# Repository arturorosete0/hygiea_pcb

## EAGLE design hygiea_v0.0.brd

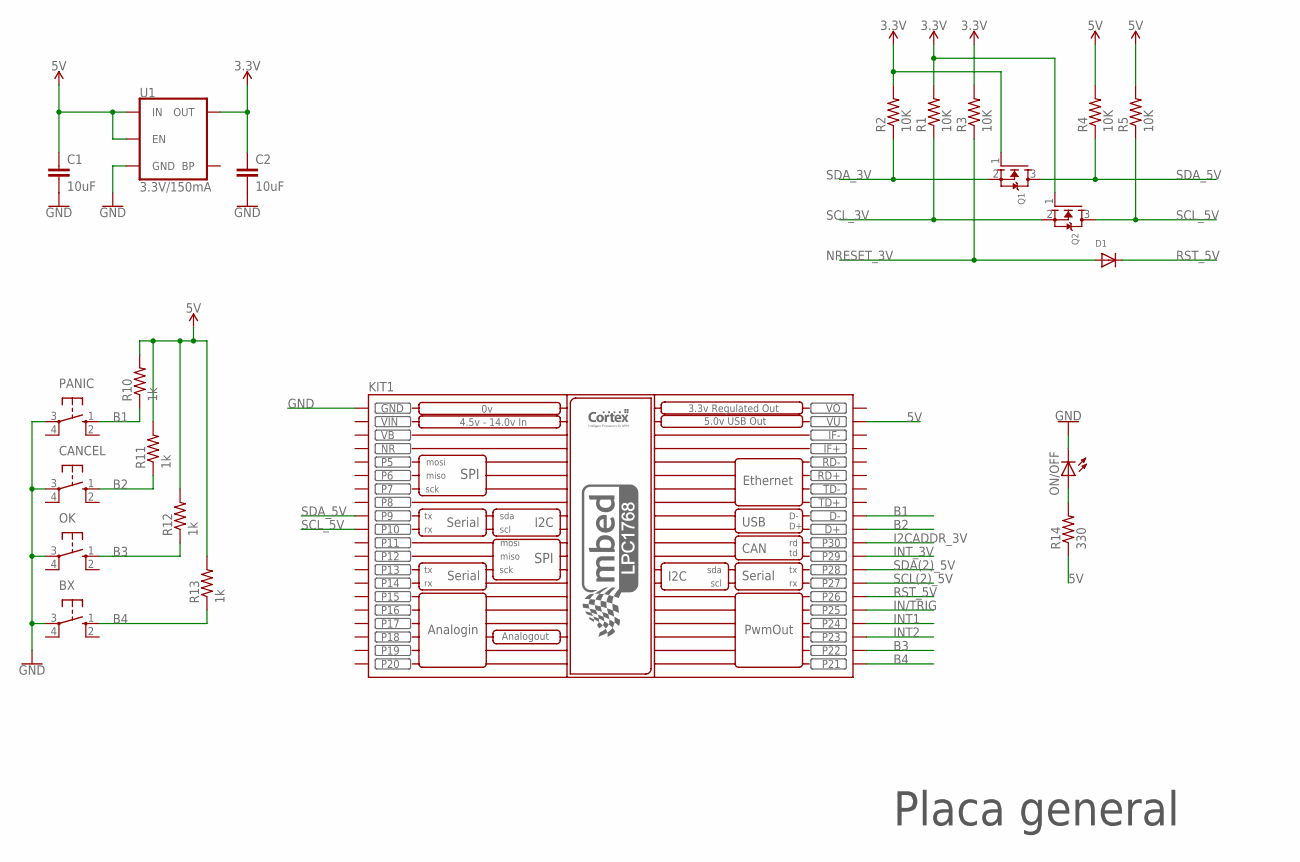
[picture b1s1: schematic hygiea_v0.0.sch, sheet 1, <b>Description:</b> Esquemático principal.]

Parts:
BX: 10-XX; B3F-10XX
C1, C2: 10uF; C0805
CANCEL: 10-XX; B3F-10XX
D1: DIODESOD-323F; SOD-323F
KIT1: MBED_NXP_LPC1768; MBED-KIT
OK: 10-XX; B3F-10XX
ON/OFF: LEDCHIP-LED0805; CHIP-LED0805
PANIC: 10-XX; B3F-10XX
Q1, Q2: MOSFET-NWAVE; SOT23-W
R1, R2, R3, R4, R5: 10K; R0805
R10, R11, R12, R13: 1k; R0805
R14: 330; R0805
U1: 3.3V/150mA; SOT23-5

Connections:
3.3V: C2.1, Q1.1 (G), Q2.1 (G), R1.2, R2.2, R3.2, U1.5 (OUT); also elsewhere on the board
5V: C1.1, KIT1.VU, R4.2, R5.2, R10.2, R11.2, R12.2, R13.2, R14.1, U1.1 (IN), U1.3 (EN); also elsewhere on the board
B1: KIT1.D-, PANIC.1 (S), R10.1
B2: CANCEL.1 (S), KIT1.D+, R11.1
B3: KIT1.P$22 (P22), OK.1 (S), R12.1
B4: BX.1 (S), KIT1.P$21 (P21), R13.1
GND: BX.3, C1.2, C2.2, CANCEL.3, KIT1.GND, OK.3, ON/OFF.C, PANIC.3, U1.2 (GND); also elsewhere on the board
I2CADDR_3V: KIT1.P$30 (P30); also elsewhere on the board
IN/TRIG: KIT1.P$25 (P25); also elsewhere on the board
INT1: KIT1.P$24 (P24); also elsewhere on the board
INT2: KIT1.P$23 (P23); also elsewhere on the board
INT_3V: KIT1.P$29 (P29); also elsewhere on the board
unnamed: ON/OFF.A, R14.2
NR: KIT1.NR
NRESET_3V: D1.A, R3.1; also elsewhere on the board
RST_5V: D1.C, KIT1.P$26 (P26)
SCL(2)_5V: KIT1.P$27 (P27); also elsewhere on the board
SCL_3V: Q2.2 (S), R1.1; also elsewhere on the board
SCL_5V: KIT1.P$10 (P10), Q2.3 (D), R5.1; also elsewhere on the board
SDA(2)_5V: KIT1.P$28 (P28); also elsewhere on the board
SDA_3V: Q1.2 (S), R2.1; also elsewhere on the board
SDA_5V: KIT1.P$9 (P9), Q1.3 (D), R4.1; also elsewhere on the board
VB: KIT1.VB
VIN: KIT1.VIN
VO: KIT1.VOUT (VO)

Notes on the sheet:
Placa general

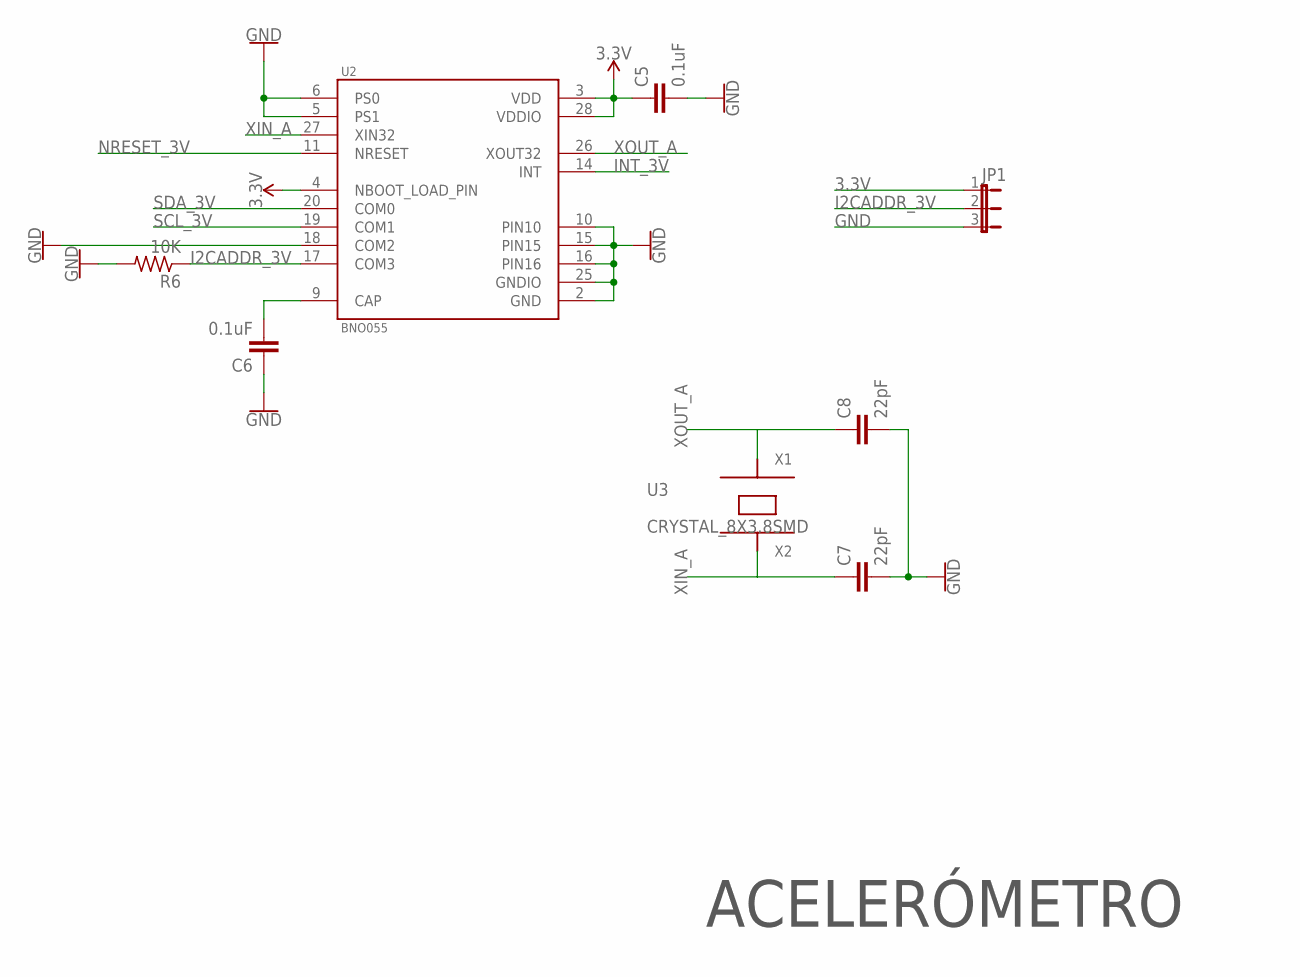
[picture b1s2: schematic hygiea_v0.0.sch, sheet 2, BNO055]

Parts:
C5, C6: 0.1uF; C0805
C7, C8: 22pF; C0805
JP1: JP2E; JP2
R6: 10K; R0805
U2: BNO055; LGA28R50P4X10_380X520X100
U3: CRYSTAL_8X3.8SMD; PM8.0X3.8MM

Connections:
3.3V: C5.1, JP1.1, U2.3 (VDD), U2.4 (NBOOT_LOAD_PIN), U2.28 (VDDIO); also elsewhere on the board
GND: C5.2, C6.1, C7.2, C8.2, JP1.3, R6.2, U2.2 (GND), U2.5 (PS1), U2.6 (PS0), U2.10 (PIN10), U2.15 (PIN15), U2.16 (PIN16), U2.18 (COM2), U2.25 (GNDIO); also elsewhere on the board
I2CADDR_3V: JP1.2, R6.1, U2.17 (COM3); also elsewhere on the board
INT_3V: U2.14 (INT); also elsewhere on the board
unnamed: C6.2, U2.9 (CAP)
NRESET_3V: U2.11 (NRESET); also elsewhere on the board
SCL_3V: U2.19 (COM1); also elsewhere on the board
SDA_3V: U2.20 (COM0); also elsewhere on the board
XIN_A: C7.1, U2.27 (XIN32), U3.4 (X2)
XOUT_A: C8.1, U2.26 (XOUT32), U3.1 (X1)

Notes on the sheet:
ACELERÓMETRO

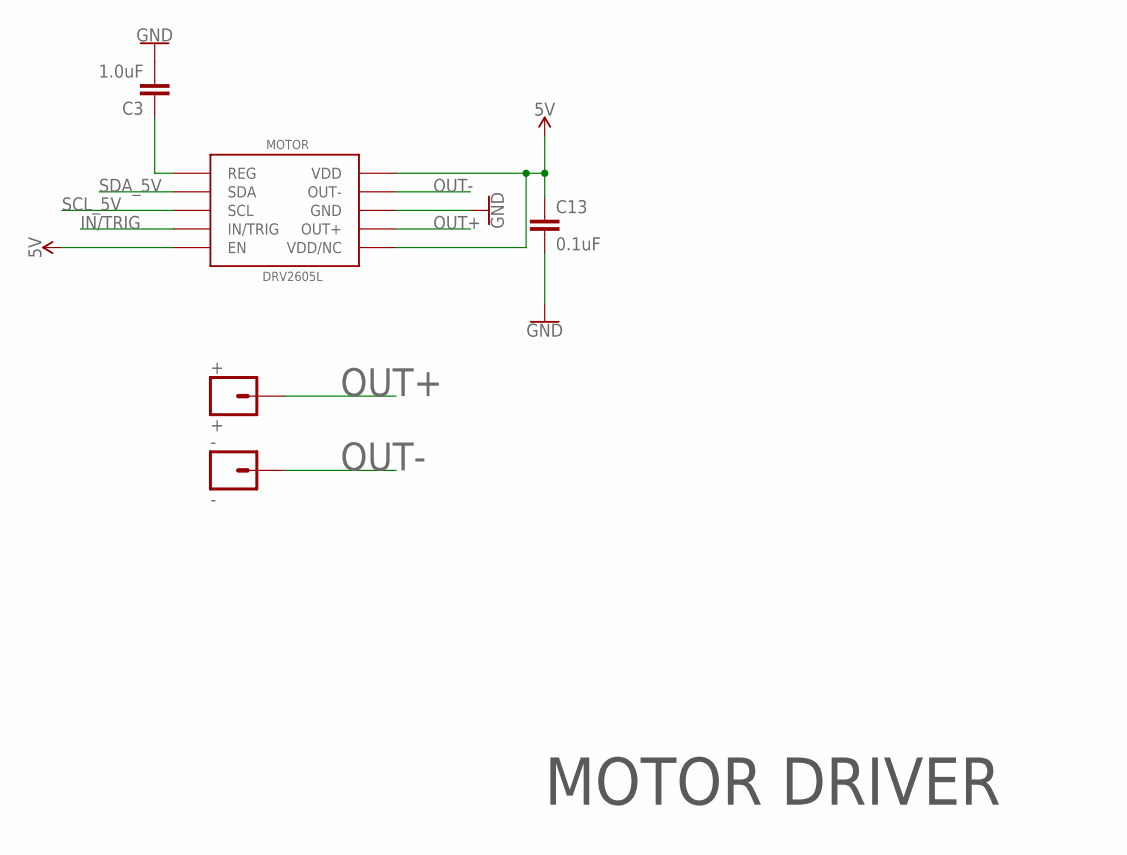
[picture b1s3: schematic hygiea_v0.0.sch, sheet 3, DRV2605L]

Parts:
+: +; 1X01_OFFSET
-: -; 1X01_OFFSET
C3: 1.0uF; C0805
C13: 0.1uF; C0805
MOTOR: DRV2605L; VSSOP-10

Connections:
5V: C13.1, MOTOR.P$5 (EN), MOTOR.P$6 (VDD/NC), MOTOR.P$10 (VDD); also elsewhere on the board
GND: C3.2, C13.2, MOTOR.P$8 (GND); also elsewhere on the board
IN/TRIG: MOTOR.P$4 (IN/TRIG); also elsewhere on the board
unnamed: C3.1, MOTOR.P$1 (REG)
OUT+: +.1, MOTOR.P$7 (OUT+)
OUT-: -.1, MOTOR.P$9 (OUT-)
SCL_5V: MOTOR.P$2 (SCL); also elsewhere on the board
SDA_5V: MOTOR.P$3 (SDA); also elsewhere on the board

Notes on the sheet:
MOTOR DRIVER

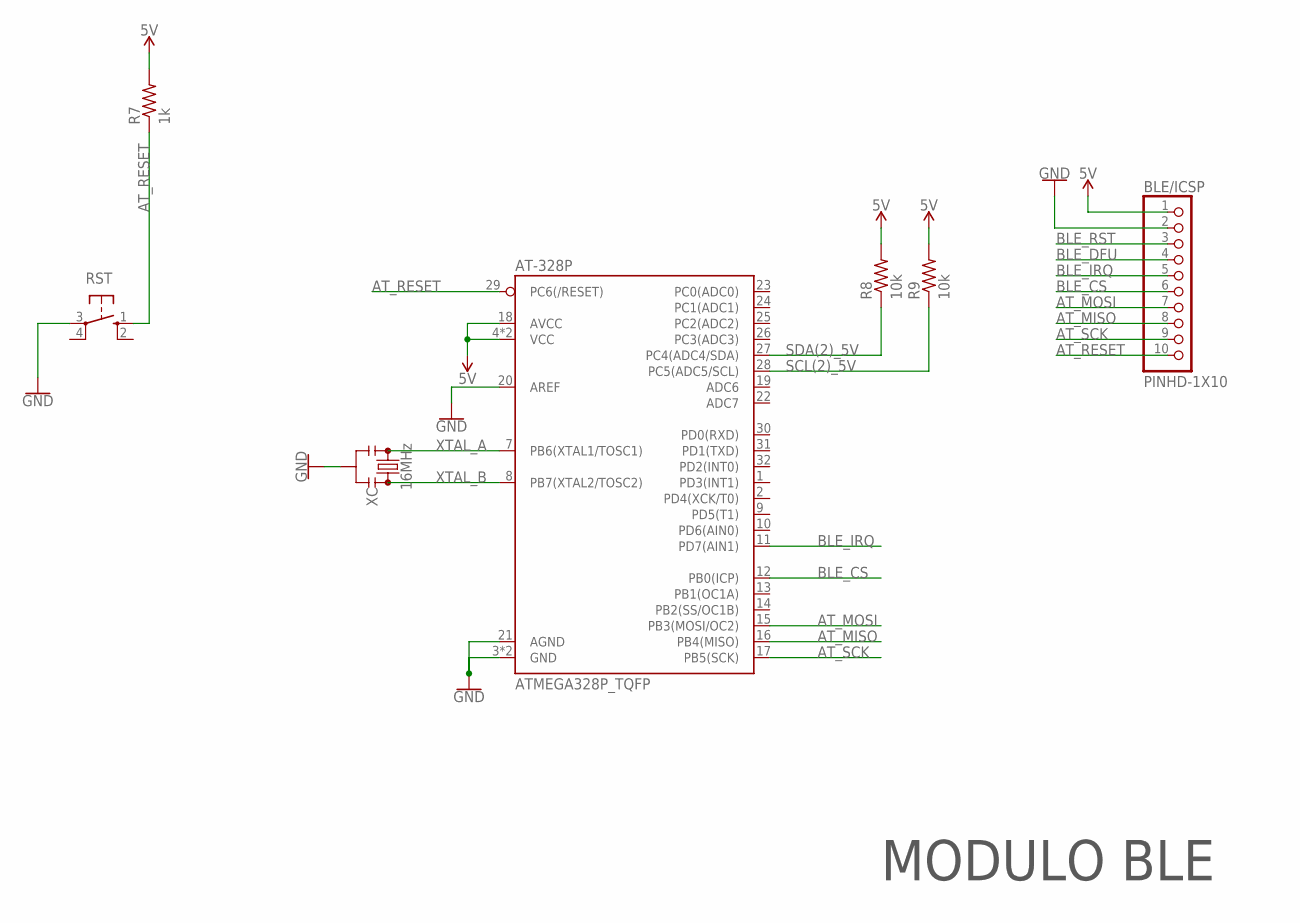
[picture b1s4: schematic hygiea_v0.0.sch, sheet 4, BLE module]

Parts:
AT-328P: ATMEGA328P_TQFP; TQFP32-08
BLE/ICSP: PINHD-1X10; 1X10-BIG
R7: 1k; R0805
R8, R9: 10k; R0805
RST: 10-XX; B3F-10XX
XC: 16MHz; RESONATOR-SMD-3.2X1.3

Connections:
5V: AT-328P.4 (VCC), AT-328P.6 (VCC), AT-328P.18 (AVCC), BLE/ICSP.1, R7.2, R8.2, R9.2; also elsewhere on the board
AT_MISO: AT-328P.16 (PB4(MISO)), BLE/ICSP.8
AT_MOSI: AT-328P.15 (PB3(MOSI/OC2)), BLE/ICSP.7
AT_RESET: AT-328P.29 (PC6(/RESET)), BLE/ICSP.10, R7.1, RST.1 (S)
AT_SCK: AT-328P.17 (PB5(SCK)), BLE/ICSP.9
BLE_CS: AT-328P.12 (PB0(ICP)), BLE/ICSP.6
BLE_DFU: BLE/ICSP.4
BLE_IRQ: AT-328P.11 (PD7(AIN1)), BLE/ICSP.5
BLE_RST: BLE/ICSP.3
GND: AT-328P.3 (GND), AT-328P.5 (GND), AT-328P.20 (AREF), AT-328P.21 (AGND), BLE/ICSP.2, RST.3, XC.2; also elsewhere on the board
SCL(2)_5V: AT-328P.28 (PC5(ADC5/SCL)), R9.1; also elsewhere on the board
SDA(2)_5V: AT-328P.27 (PC4(ADC4/SDA)), R8.1; also elsewhere on the board
XTAL_A: AT-328P.7 (PB6(XTAL1/TOSC1)), XC.3
XTAL_B: AT-328P.8 (PB7(XTAL2/TOSC2)), XC.1

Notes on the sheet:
MODULO BLE

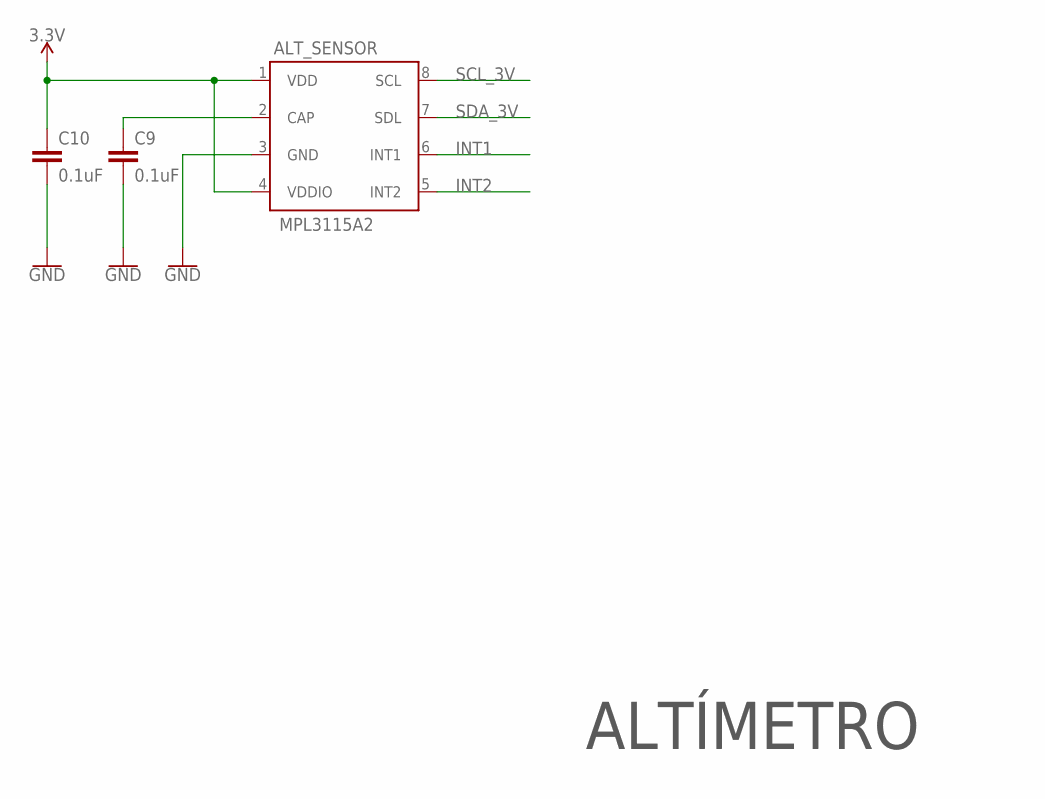
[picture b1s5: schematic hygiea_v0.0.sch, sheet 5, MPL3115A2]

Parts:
ALT_SENSOR: MPL3115A2; LGA8
C9, C10: 0.1uF; C0805

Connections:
3.3V: ALT_SENSOR.1 (VDD), ALT_SENSOR.4 (VDDIO), C10.1; also elsewhere on the board
GND: ALT_SENSOR.3 (GND), C9.2, C10.2; also elsewhere on the board
INT1: ALT_SENSOR.6 (INT1); also elsewhere on the board
INT2: ALT_SENSOR.5 (INT2); also elsewhere on the board
unnamed: ALT_SENSOR.2 (CAP), C9.1
SCL_3V: ALT_SENSOR.8 (SCL); also elsewhere on the board
SDA_3V: ALT_SENSOR.7 (SDL); also elsewhere on the board

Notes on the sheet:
ALTÍMETRO

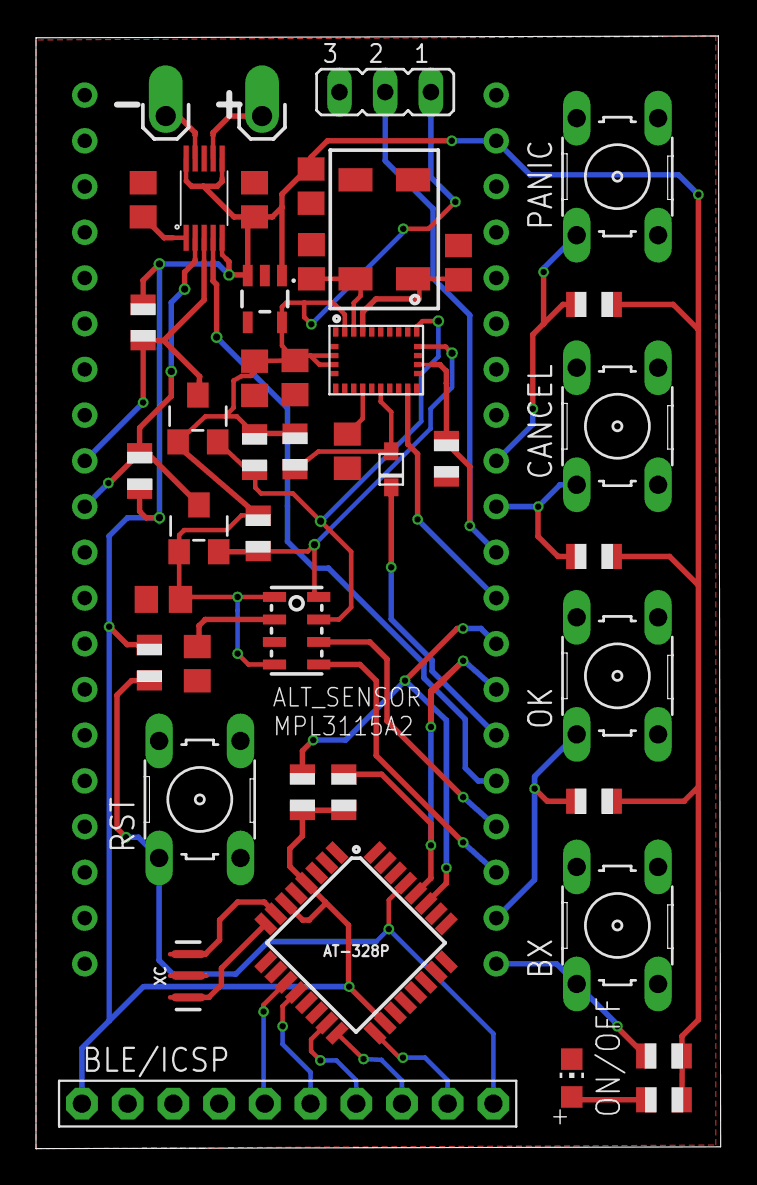
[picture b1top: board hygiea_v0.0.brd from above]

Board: 2 copper layers, 38.0 x 61.8 mm, 45 parts (0 on the bottom side), 36 nets.

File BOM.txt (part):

Partlist exported from C:/Users/Arturo Rosete/Documents/eagle/HYGIEAv0.0/hygiea_v0.0.sch at 21/02/2018 02:22 p. m.

Part       Value            Device                                  Package                   Description                                                                                                                                                                                                                                             ARM DESCRIPTION                  DIGI-KEY_PART_NUMBER DIGI-KEY_PURCHASE_URL                                                                                                                                                       MF    MP     PACKAGE      PROD_ID    SF_SKU    SPICEPREFIX VALUE          
+          +                CONN_01OFFSET                           1X01_OFFSET               Single connection point. Often used as Generic Header-pin footprint for 0.1 inch spaced/style header connections                                                                                                                                                                                                                                                                                                                                                                                                                                                    
-          -                CONN_01OFFSET                           1X01_OFFSET               Single connection point. Often used as Generic Header-pin footprint for 0.1 inch spaced/style header connections                                                                                                                                                                                                                                                                                                                                                                                                                                                    
ALT_SENSOR MPL3115A2        MPL3115A2                               LGA8                                                                                                                                                                                                                                                                                                                                                                                                                                                                                                                                                                                          
AT-328P    ATMEGA328P_TQFP  ATMEGA328P_TQFP                         TQFP32-08                 Popular 328P in QFP                                                                                                                                                                                                                                                                                                                                                                                                                                                                                                 IC-09069                         ATMEGA328P_TQFP
BLE/ICSP   PINHD-1X10       PINHD-1X10                              1X10-BIG                  Pin header 1x10 0.1" spacing                                                                                                                                                                                                                                                                                                                                                                                                                                                                                                                                        
C1         10uF             C-EUC0805                               C0805                     CAPACITOR, European symbol                                                                                                                                                                                                                                                                                                                                                                                                                                                                                                               C                          
C2         10uF             C-EUC0805                               C0805                     CAPACITOR, European symbol                                                                                                                                                                                                                                                                                                                                                                                                                                                                                                               C                          
C3         1.0uF            C-EUC0805                               C0805                     CAPACITOR, European symbol                                                                                                                                                                                                                                                                                                                                                                                                                                                                                                               C                          
C5         0.1uF            C-EUC0805                               C0805                     CAPACITOR, European symbol                                                                                                                                                                                                                                                                                                                                                                                                                                                                                                               C                          
C6         0.1uF            C-EUC0805                               C0805                     CAPACITOR, European symbol                                                                                                                                                                                                                                                                                                                                                                                                                                                                                                               C                          
C7         22pF             C-EUC0805                               C0805                     CAPACITOR, European symbol                                                                                                                                                                                                                                                                                                                                                                                                                                                                                                               C                          
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
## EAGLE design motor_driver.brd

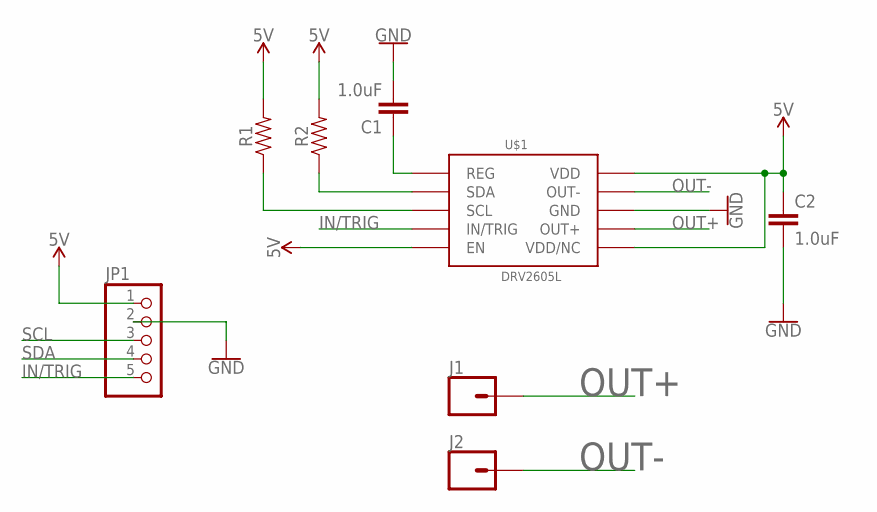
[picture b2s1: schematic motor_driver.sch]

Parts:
C1, C2: 1.0uF; 0805
J1, J2: CONN_01OFFSET; 1X01_OFFSET
JP1: PINHD-1X5; 1X05
R1, R2: 0805
U$1: DRV2605L; VSSOP-10

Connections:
5V: C2.1, JP1.1, R1.2, R2.2, U$1.P$5 (EN), U$1.P$6 (VDD/NC), U$1.P$10 (VDD)
GND: C1.2, C2.2, JP1.2, U$1.P$8 (GND)
IN/TRIG: JP1.5, U$1.P$4 (IN/TRIG)
unnamed: C1.1, U$1.P$1 (REG)
OUT+: J1.1, U$1.P$7 (OUT+)
OUT-: J2.1, U$1.P$9 (OUT-)
SCL: JP1.3, R1.1, U$1.P$2 (SCL)
SDA: JP1.4, R2.1, U$1.P$3 (SDA)

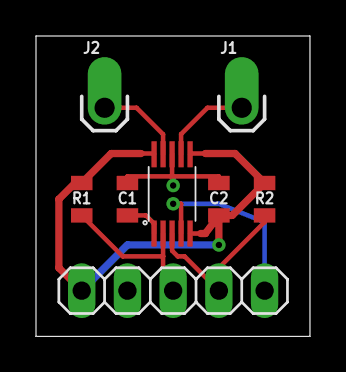
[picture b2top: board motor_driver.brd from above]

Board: 2 copper layers, 15.2 x 16.7 mm, 8 parts (0 on the bottom side), 8 nets.

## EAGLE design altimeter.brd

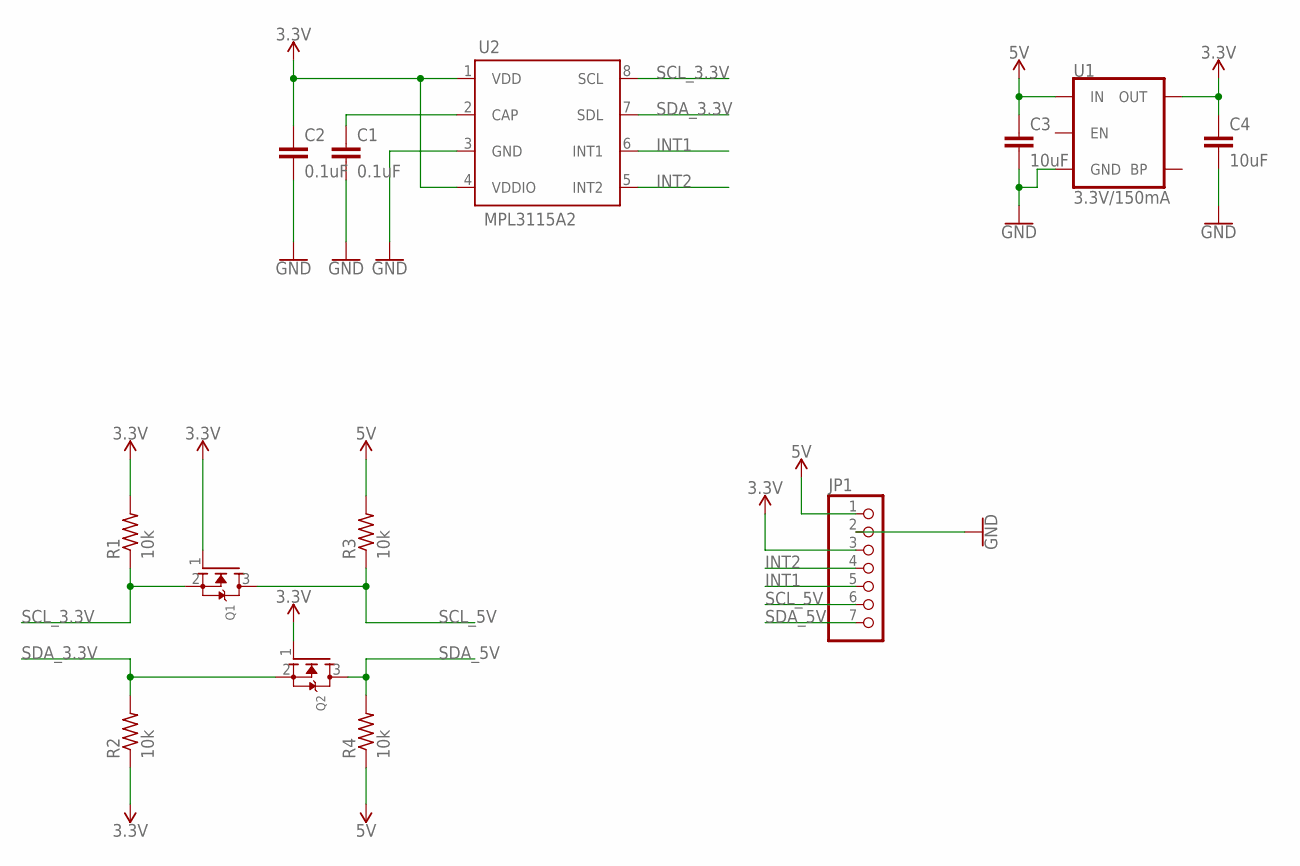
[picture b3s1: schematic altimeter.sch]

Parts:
C1, C2: 0.1uF; C0805
C3, C4: 10uF; C0805
JP1: PINHD-1X7; 1X07
Q1, Q2: MOSFET-NWAVE; SOT23-W
R1, R2, R3, R4: 10k; R0805
U1: 3.3V/150mA; SOT23-5
U2: MPL3115A2; LGA8

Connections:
3.3V: C2.1, C4.1, JP1.3, Q1.1 (G), Q2.1 (G), R1.2, R2.1, U1.5 (OUT), U2.1 (VDD), U2.4 (VDDIO)
5V: C3.1, JP1.1, R3.2, R4.1, U1.1 (IN)
GND: C1.2, C2.2, C3.2, C4.2, JP1.2, U1.2 (GND), U2.3 (GND)
INT1: JP1.5, U2.6 (INT1)
INT2: JP1.4, U2.5 (INT2)
unnamed: C1.1, U2.2 (CAP)
SCL_3.3V: Q1.2 (S), R1.1, U2.8 (SCL)
SCL_5V: JP1.6, Q1.3 (D), R3.1
SDA_3.3V: Q2.2 (S), R2.2, U2.7 (SDL)
SDA_5V: JP1.7, Q2.3 (D), R4.2

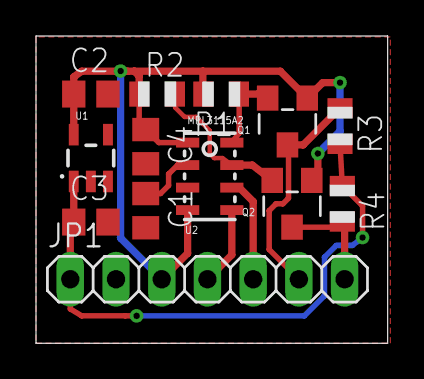
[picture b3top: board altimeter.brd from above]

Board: 2 copper layers, 19.5 x 17.1 mm, 13 parts (0 on the bottom side), 10 nets.

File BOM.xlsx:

Artículo | Cantidad | Valor | Paquete | Precio Unitario
Resistencia | 30 | 10k | 805 | x
 | 30 | 1k |  | x
 | 30 | 330k |  | x
Capacitor | 30 | 10uF |  | x
 | 30 | 1uF |  | x
 | 30 | 0.1uF |  | x
 | 30 | 22uF |  | x
BNO055
MPL3115A2

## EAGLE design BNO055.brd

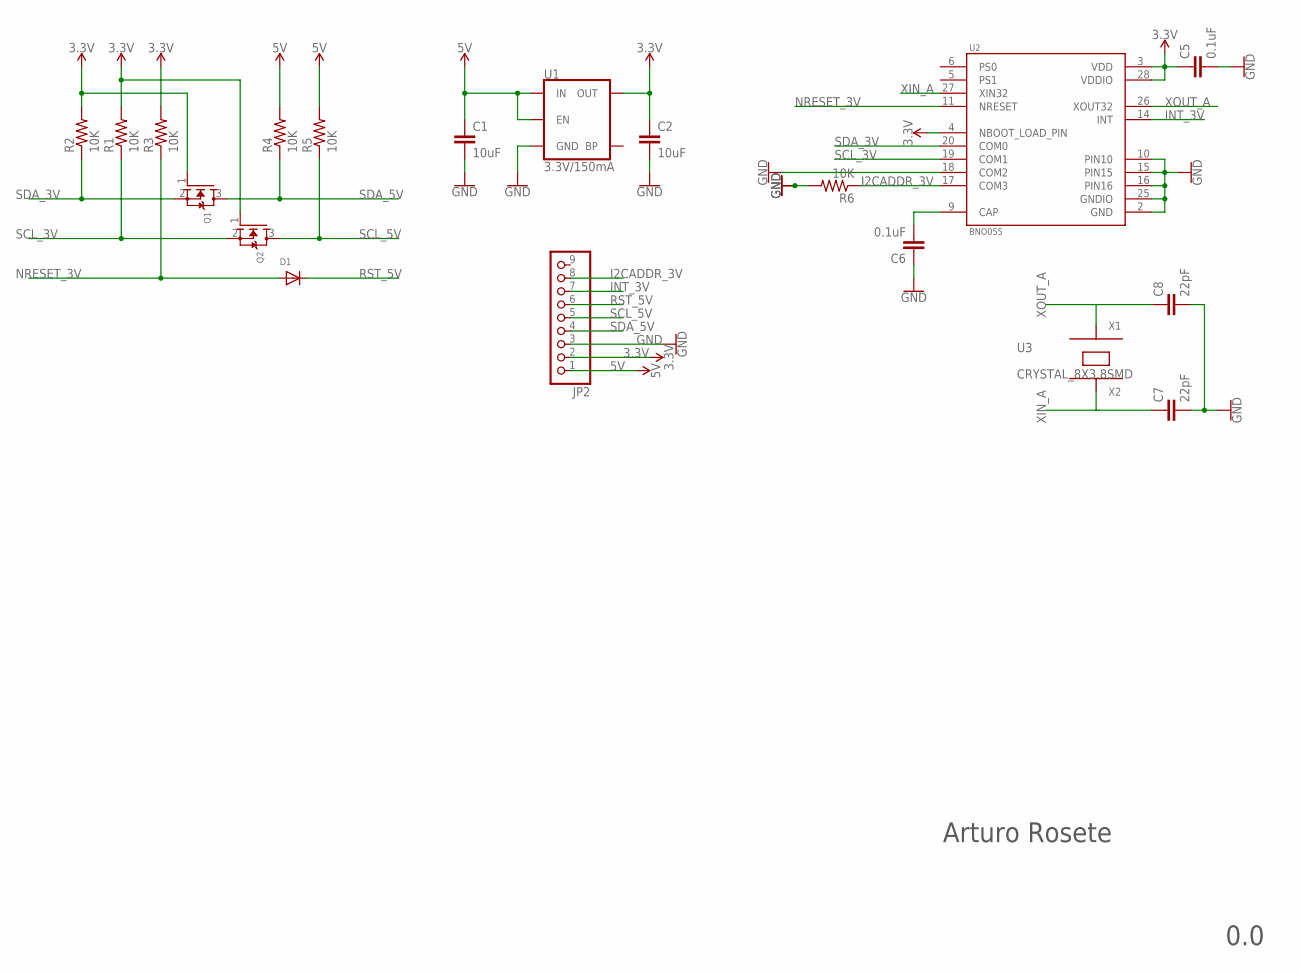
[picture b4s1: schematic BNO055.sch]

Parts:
C1, C2: 10uF; 0805
C5, C6: 0.1uF; C0805
C7, C8: 22pF; C0805
D1: DIODESOD-323F; SOD-323F
JP2: PINHD-1X9; 1X09-BIG
Q1, Q2: MOSFET-NWAVE; SOT23-W
R1, R2, R3, R4, R5, R6: 10K; R0805
U1: 3.3V/150mA; SOT23-5
U2: BNO055; LGA28R50P4X10_380X520X100
U3: CRYSTAL_8X3.8SMD; PM8.0X3.8MM

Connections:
3.3V: C2.1, C5.1, JP2.2, Q1.1 (G), Q2.1 (G), R1.2, R2.2, R3.2, U1.5 (OUT), U2.3 (VDD), U2.4 (NBOOT_LOAD_PIN), U2.28 (VDDIO)
5V: C1.1, JP2.1, R4.2, R5.2, U1.1 (IN), U1.3 (EN)
GND: C1.2, C2.2, C5.2, C6.1, C7.2, C8.2, JP2.3, R6.2, U1.2 (GND), U2.2 (GND), U2.10 (PIN10), U2.15 (PIN15), U2.16 (PIN16), U2.18 (COM2), U2.25 (GNDIO)
I2CADDR_3V: JP2.8, R6.1, U2.17 (COM3)
INT_3V: JP2.7, U2.14 (INT)
unnamed: C6.2, U2.9 (CAP)
NRESET_3V: D1.A, R3.1, U2.11 (NRESET)
RST_5V: D1.C, JP2.6
SCL_3V: Q2.2 (S), R1.1, U2.19 (COM1)
SCL_5V: JP2.5, Q2.3 (D), R5.1
SDA_3V: Q1.2 (S), R2.1, U2.20 (COM0)
SDA_5V: JP2.4, Q1.3 (D), R4.1
XIN_A: C7.1, U2.27 (XIN32), U3.4 (X2)
XOUT_A: C8.1, U2.26 (XOUT32), U3.1 (X1)

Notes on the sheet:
Arturo Rosete
0.0

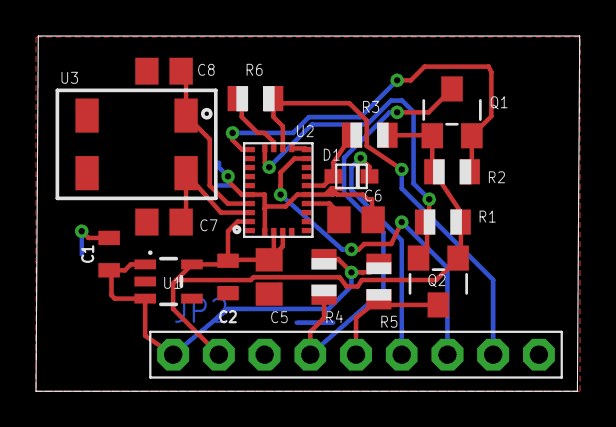
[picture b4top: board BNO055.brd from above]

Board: 2 copper layers, 30.2 x 19.7 mm, 19 parts (0 on the bottom side), 14 nets.

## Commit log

2018-02-20 Segundo test
2018-02-20 Se movió la resistencia del crystal del BNO055
2018-02-21 Se agregó el BOM en csv
2018-02-22 Version barata, push buttons standar
2018-03-02 modificacion despues de curso eagle

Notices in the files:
parts and their libraries:
SparkFun-IC-Power: Licensing: Creative Commons ShareAlike 4.0 International - https://creativecommons.org/licenses/by-sa/4.0
